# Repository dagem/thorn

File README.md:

# thorn
A no-nonsense macropad with a rosy theme

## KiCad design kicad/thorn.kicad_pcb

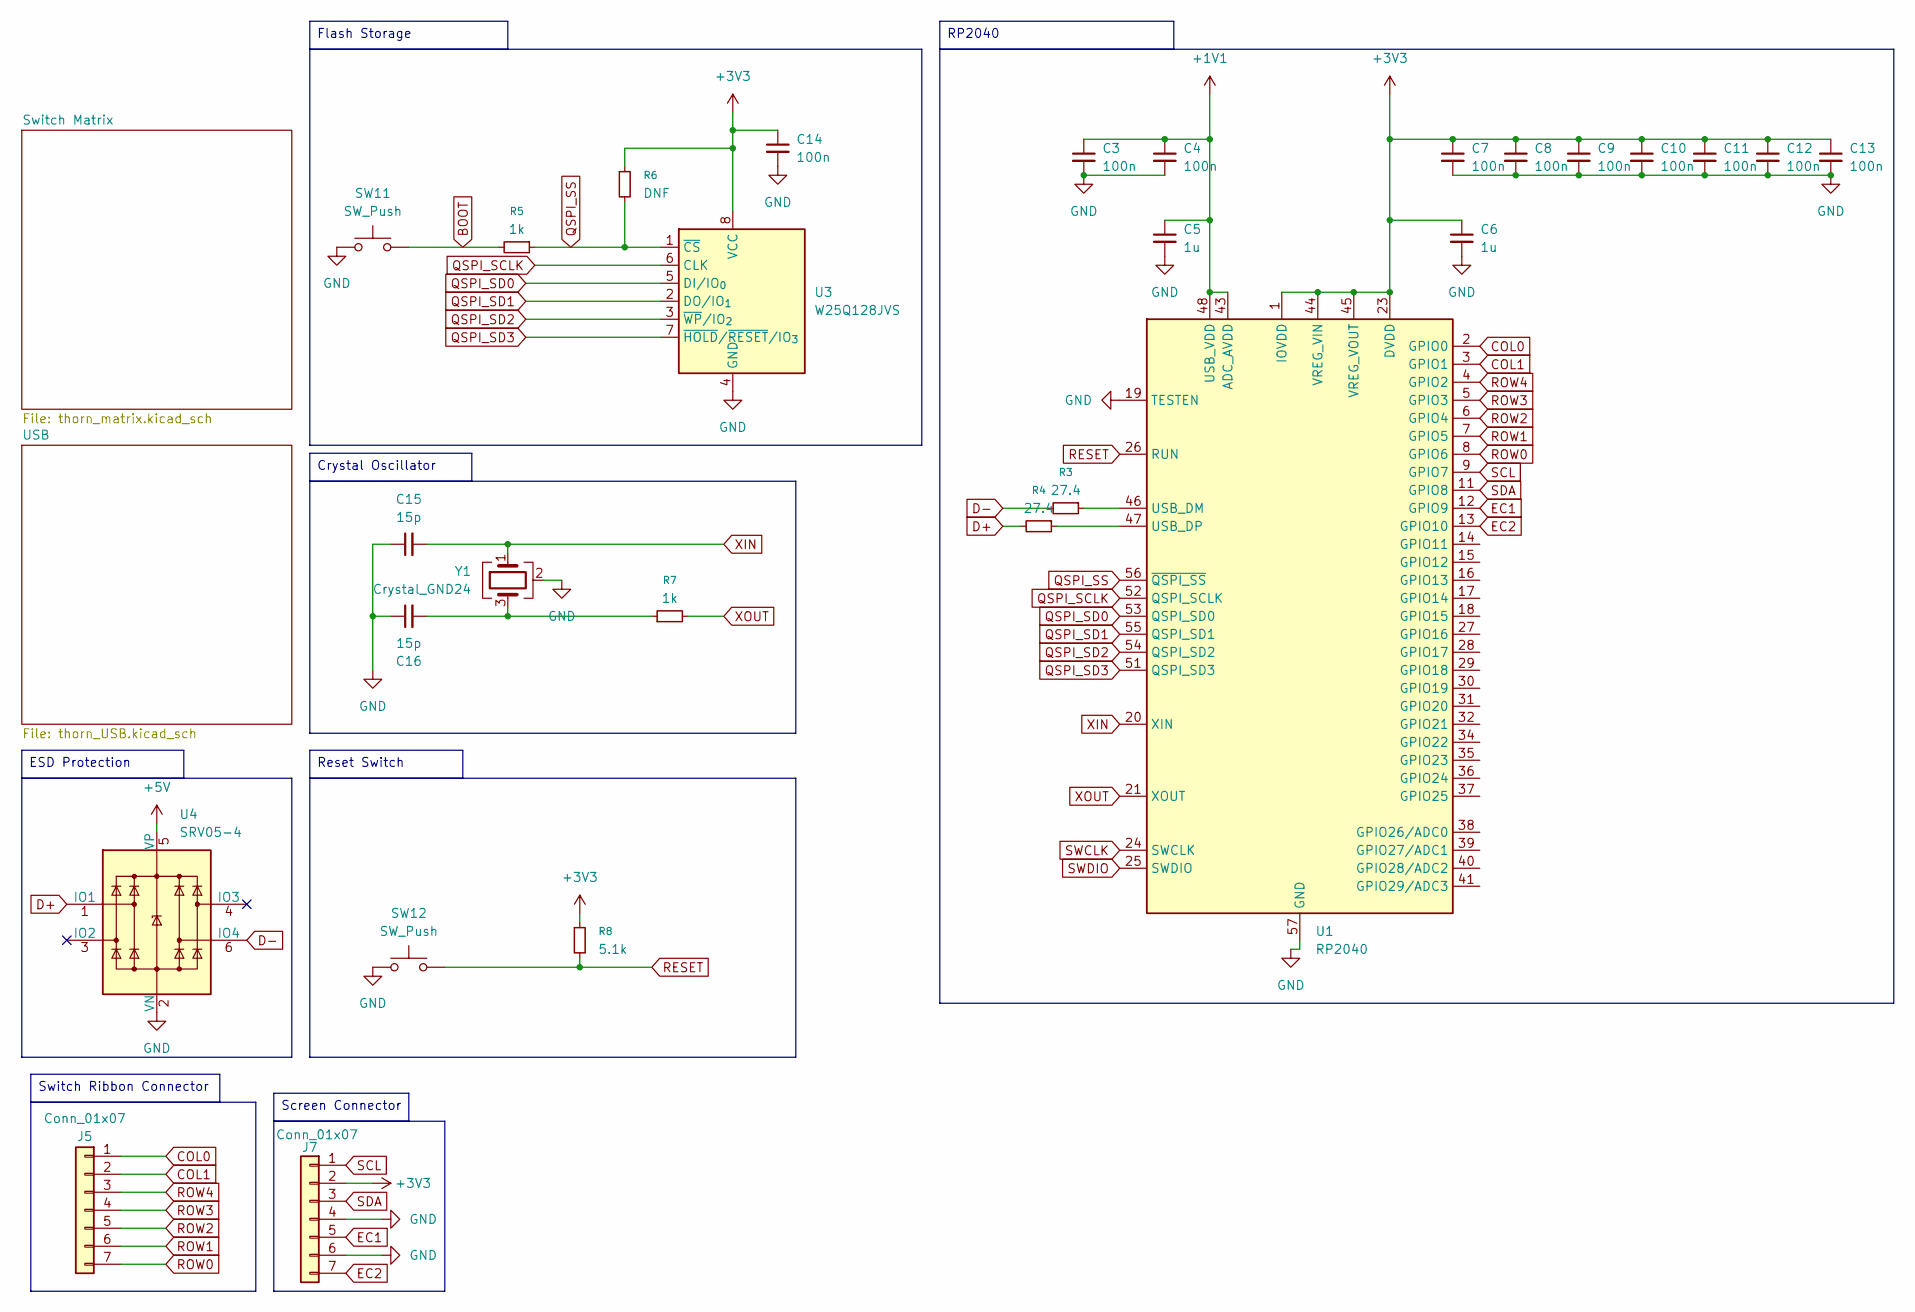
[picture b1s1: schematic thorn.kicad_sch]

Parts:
C3, C4, C7, C8, C9, C10, C11, C12, C13, C14: 100n; C_0805_2012Metric
C5, C6: 1u; C_0805_2012Metric
C15, C16: 15p; C_0805_2012Metric
J5, J7: Conn_01x07; Molex_200528-0070_1x07-1MP_P1.00mm_Horizontal
R3, R4: 27.4; R_0805_2012Metric
R5, R7: 1k; R_0805_2012Metric
R6: DNF; R_0805_2012Metric
R8: 5.1k; R_0805_2012Metric
SW11, SW12: SW_Push; SW_Push_1P1T_XKB_TS-1187A
U1: RP2040; QFN-56-1EP_7x7mm_P0.4mm_EP3.2x3.2mm
U3: W25Q128JVS; SOIC-8_5.3x5.3mm_P1.27mm
U4: SRV05-4; SOT-23-6
Y1: Crystal_GND24; Crystal_SMD_3225-4Pin_3.2x2.5mm

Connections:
+1V1: C3.1, C4.1, C5.1, U1.43 (ADC_AVDD), U1.48 (USB_VDD)
+3V3: C6.1, C7.1, C8.1, C9.1, C10.1, C11.1, C12.1, C13.1, C14.1, J7.2, R6.1, R8.1, U1.1 (IOVDD), U1.10 (IOVDD), U1.22 (IOVDD), U1.23 (DVDD), U1.33 (IOVDD), U1.42 (IOVDD), U1.44 (VREG_VIN), U1.45 (VREG_VOUT), U1.49 (IOVDD), U1.50 (DVDD), U3.8 (VCC); also elsewhere on the board
+5V: U4.5 (VP)
BOOT: R5.2, SW11.2
COL0: J5.1, U1.2 (GPIO0); also elsewhere on the board
COL1: J5.2, U1.3 (GPIO1); also elsewhere on the board
D+: R4.2, U4.1 (IO1); also elsewhere on the board
D-: R3.2, U4.6 (IO4); also elsewhere on the board
EC1: J7.5, U1.12 (GPIO9); also elsewhere on the board
EC2: J7.7, U1.13 (GPIO10); also elsewhere on the board
GND: C3.2, C4.2, C5.2, C6.2, C7.2, C8.2, C9.2, C10.2, C11.2, C12.2, C13.2, C14.2, C15.1, C16.1, J7.4, J7.6, SW11.1, SW12.1, U1.19 (TESTEN), U1.57 (GND), U3.4 (GND), U4.2 (VN), Y1.2 (G), Y1.4 (G); also elsewhere on the board
unnamed: C16.2, R7.1, Y1.3
unnamed: R3.1, U1.46 (USB_DM)
unnamed: R4.1, U1.47 (USB_DP)
QSPI_SCLK: U1.52 (QSPI_SCLK), U3.6 (CLK)
QSPI_SD0: U1.53 (QSPI_SD0), U3.5 (DI/IO_{0})
QSPI_SD1: U1.55 (QSPI_SD1), U3.2 (DO/IO_{1})
QSPI_SD2: U1.54 (QSPI_SD2), U3.3 (~WP/IO_{2})
QSPI_SD3: U1.51 (QSPI_SD3), U3.7 (~HOLD/~RESET/IO_{3})
QSPI_SS: R5.1, R6.2, U1.56 (~QSPI_SS), U3.1 (~CS)
RESET: R8.2, SW12.2, U1.26 (RUN)
ROW0: J5.7, U1.8 (GPIO6); also elsewhere on the board
ROW1: J5.6, U1.7 (GPIO5); also elsewhere on the board
ROW2: J5.5, U1.6 (GPIO4); also elsewhere on the board
ROW3: J5.4, U1.5 (GPIO3); also elsewhere on the board
ROW4: J5.3, U1.4 (GPIO2); also elsewhere on the board
SCL: J7.1, U1.9 (GPIO7); also elsewhere on the board
SDA: J7.3, U1.11 (GPIO8); also elsewhere on the board
SWCLK: U1.24 (SWCLK)
SWDIO: U1.25 (SWDIO)
XIN: C15.2, U1.20 (XIN), Y1.1
XOUT: R7.2, U1.21 (XOUT)

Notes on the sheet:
Switch Ribbon Connector
Crystal Oscillator
Flash Storage
ESD Protection
RP2040
Screen Connector
Reset Switch

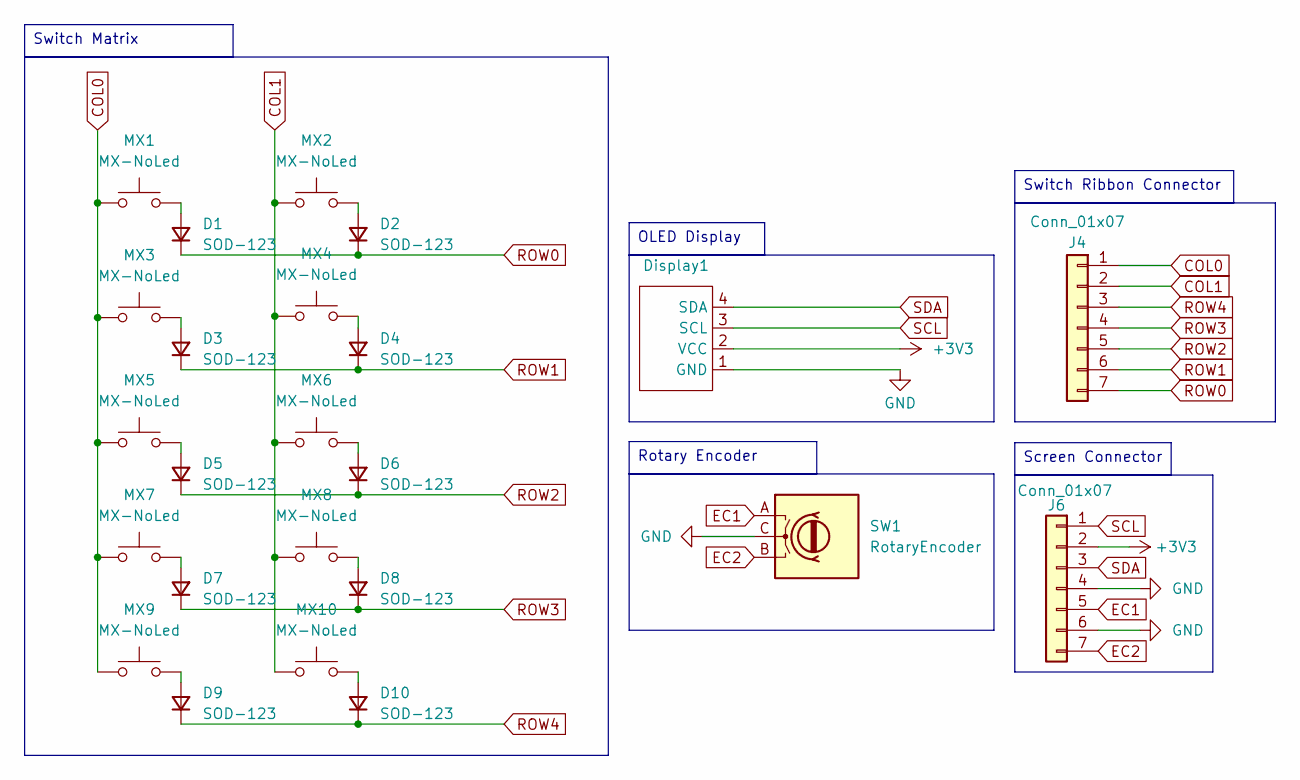
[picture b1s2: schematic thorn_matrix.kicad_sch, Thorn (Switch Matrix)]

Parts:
D1, D2, D3, D4, D5, D6, D7, D8, D9, D10: SOD-123; D_SOD-123
Display1: HS91L02W2C01
J4, J6: Conn_01x07; Molex_200528-0070_1x07-1MP_P1.00mm_Horizontal
MX1, MX2, MX3, MX4, MX5, MX6, MX7, MX8, MX9, MX10: MX-NoLed; MXOnly-1U-NoLED
SW1: RotaryEncoder; RotaryEncoder_Alps_EC12E_Vertical_H20mm

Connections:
+3V3: Display1.2 (VCC), J6.2; also elsewhere on the board
COL0: J4.1, MX1.1, MX3.1, MX5.1, MX7.1, MX9.1; also elsewhere on the board
COL1: J4.2, MX2.1, MX4.1, MX6.1, MX8.1, MX10.1; also elsewhere on the board
EC1: J6.5, SW1.A; also elsewhere on the board
EC2: J6.7, SW1.B; also elsewhere on the board
GND: Display1.1 (GND), J6.4, J6.6, SW1.C; also elsewhere on the board
unnamed: D1.2 (A), MX1.2
unnamed: D2.2 (A), MX2.2
unnamed: D3.2 (A), MX3.2
unnamed: D4.2 (A), MX4.2
unnamed: D5.2 (A), MX5.2
unnamed: D6.2 (A), MX6.2
unnamed: D7.2 (A), MX7.2
unnamed: D8.2 (A), MX8.2
unnamed: D9.2 (A), MX9.2
unnamed: D10.2 (A), MX10.2
ROW0: D1.1 (K), D2.1 (K), J4.7; also elsewhere on the board
ROW1: D3.1 (K), D4.1 (K), J4.6; also elsewhere on the board
ROW2: D5.1 (K), D6.1 (K), J4.5; also elsewhere on the board
ROW3: D7.1 (K), D8.1 (K), J4.4; also elsewhere on the board
ROW4: D9.1 (K), D10.1 (K), J4.3; also elsewhere on the board
SCL: Display1.3 (SCL), J6.1; also elsewhere on the board
SDA: Display1.4 (SDA), J6.3; also elsewhere on the board

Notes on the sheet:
OLED Display
Switch Ribbon Connector
Screen Connector
Rotary Encoder
Switch Matrix

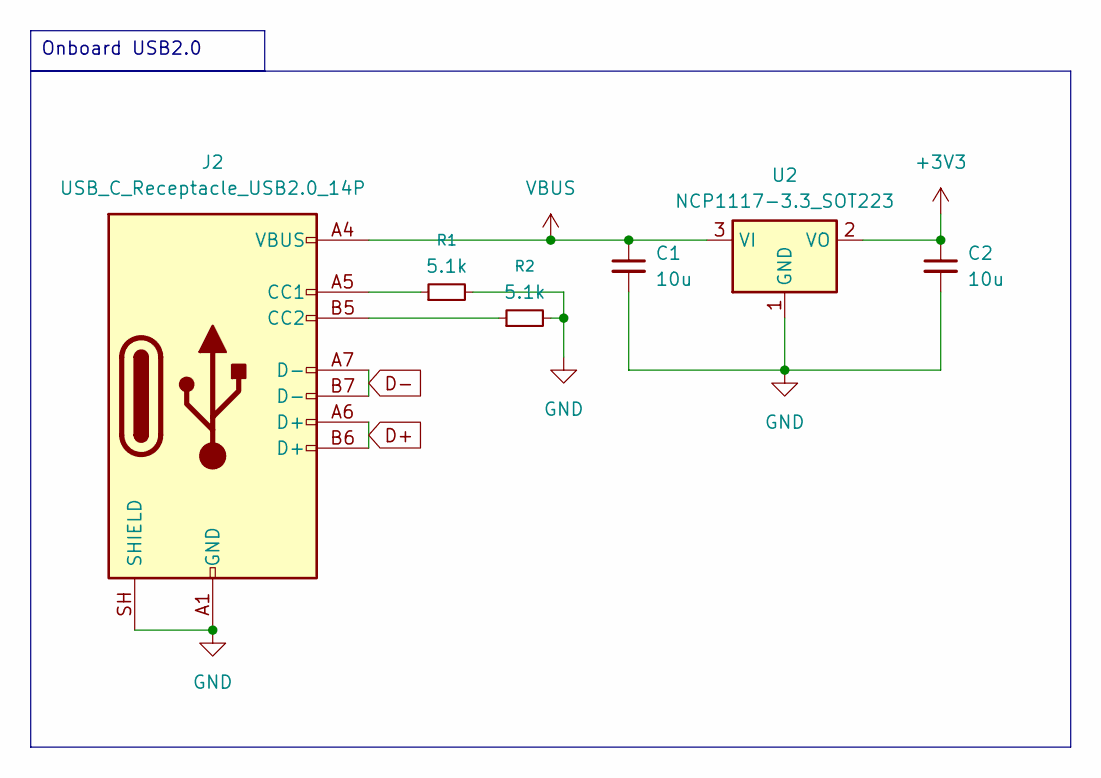
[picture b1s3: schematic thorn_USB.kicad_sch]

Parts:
C1, C2: 10u; C_0805_2012Metric
J2: USB_C_Receptacle_USB2.0_14P; USB_C_Receptacle_JAE_DX07S016JA1R1500
R1, R2: 5.1k; R_0805_2012Metric
U2: NCP1117-3.3_SOT223; SOT-223-3_TabPin2

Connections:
+3V3: C2.1, U2.2 (VO); also elsewhere on the board
D+: J2.A6 (D+), J2.B6 (D+); also elsewhere on the board
D-: J2.A7 (D-), J2.B7 (D-); also elsewhere on the board
GND: C1.2, C2.2, J2.A1 (GND), J2.A12 (GND), J2.B1 (GND), J2.B12 (GND), J2.SH (SHIELD), R1.2, R2.2, U2.1 (GND); also elsewhere on the board
unnamed: J2.A5 (CC1), R1.1
unnamed: J2.B5 (CC2), R2.1
VBUS: C1.1, J2.A4 (VBUS), J2.A9 (VBUS), J2.B4 (VBUS), J2.B9 (VBUS), U2.3 (VI)

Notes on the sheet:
Onboard USB2.0

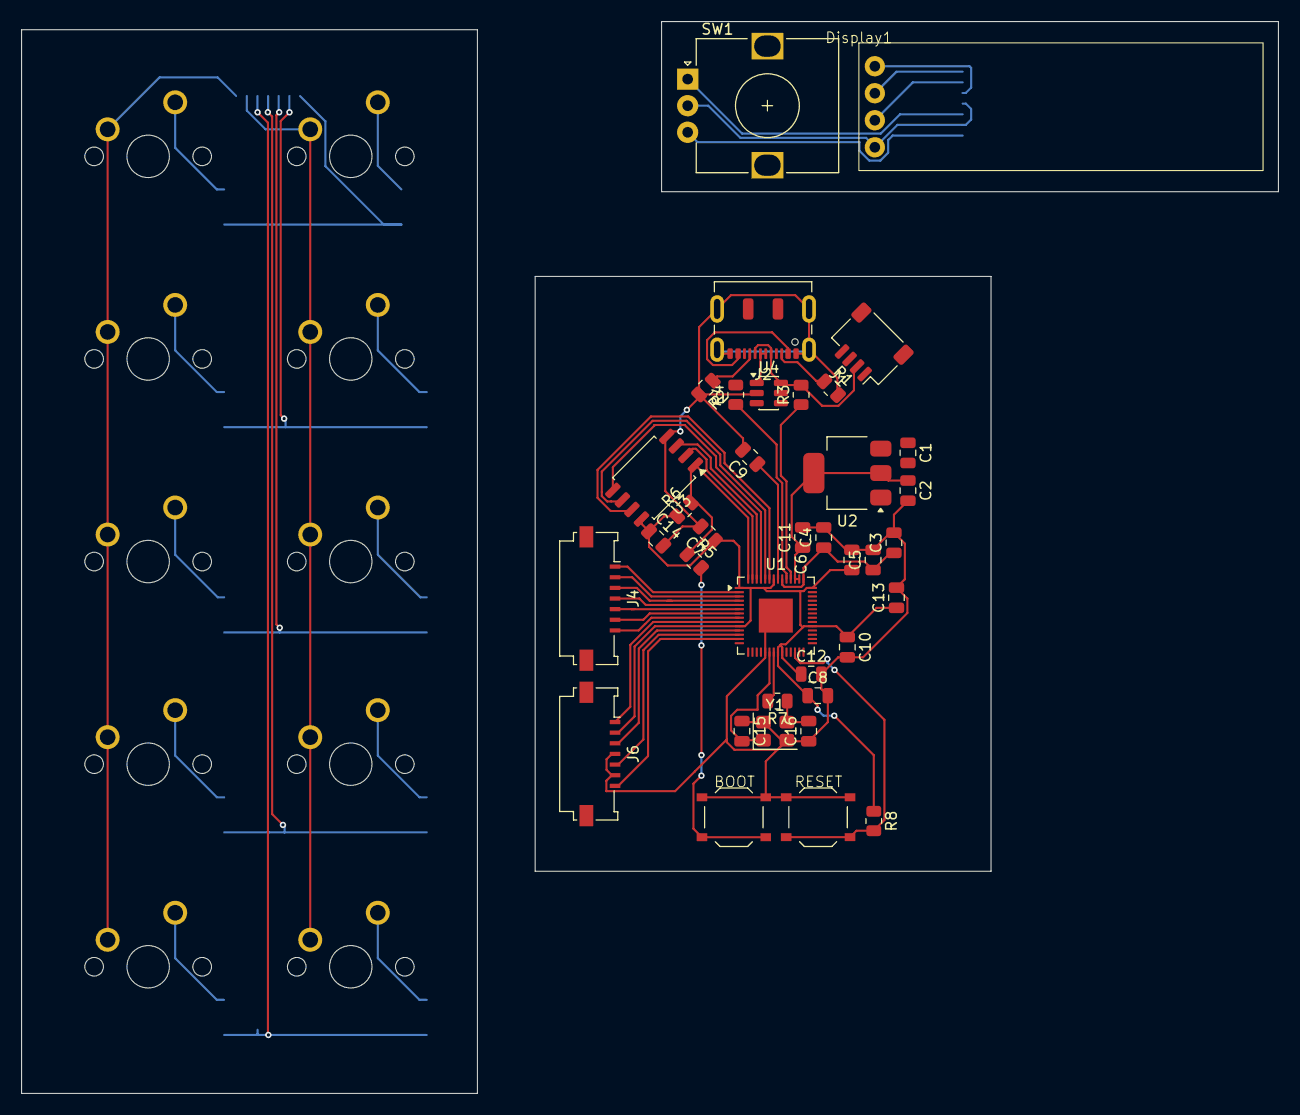
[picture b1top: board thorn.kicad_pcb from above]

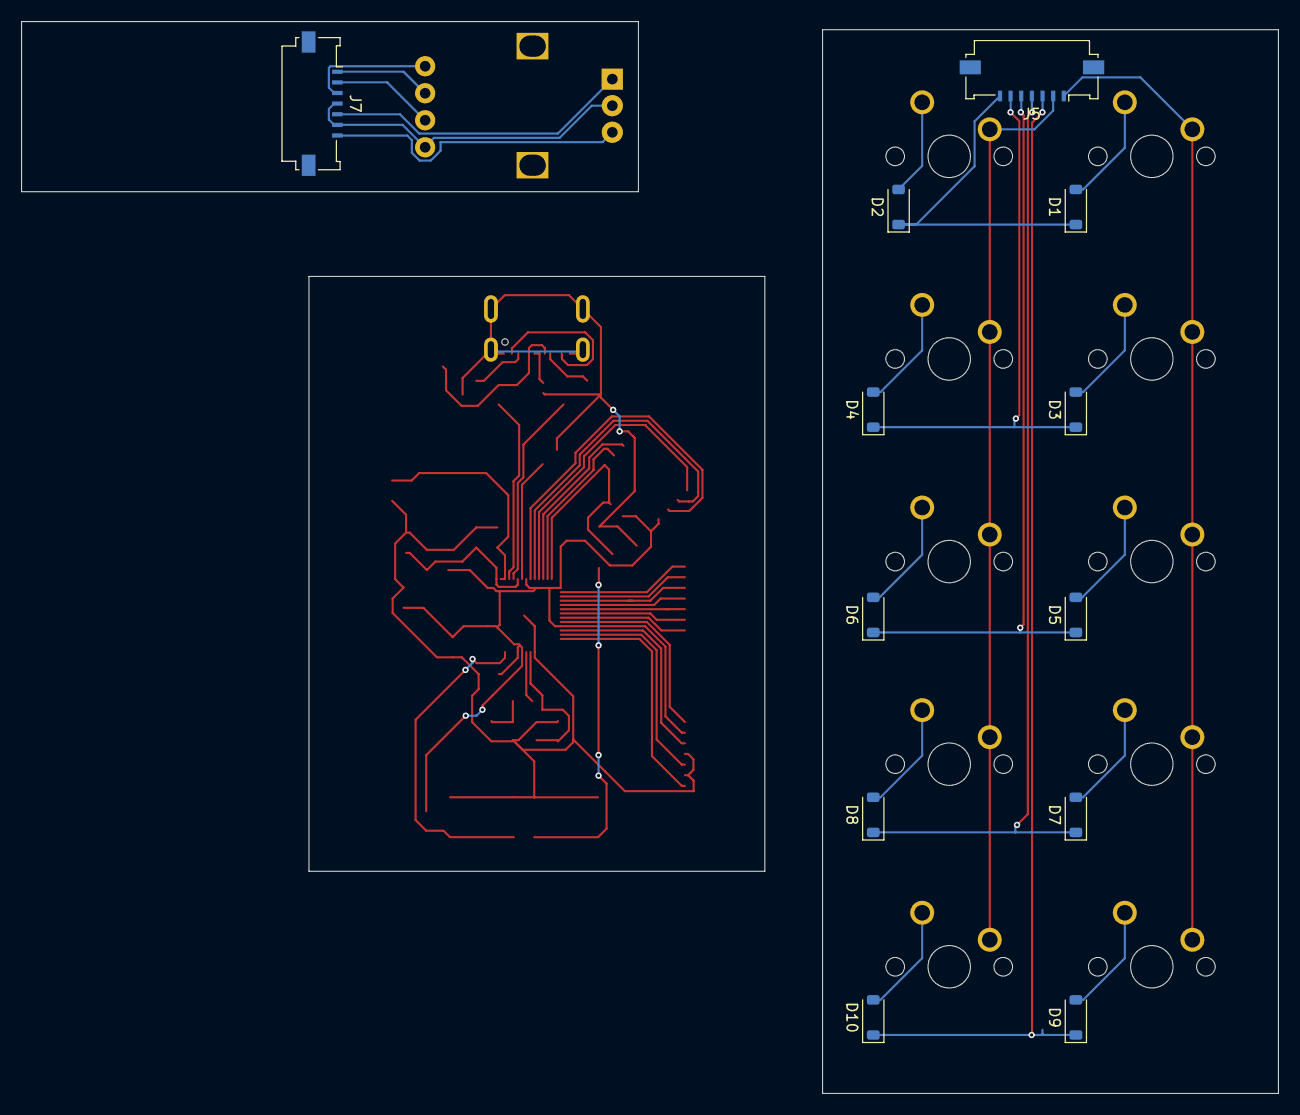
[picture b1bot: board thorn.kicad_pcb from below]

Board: 2 copper layers, 118.2 x 100.8 mm, 59 parts (12 on the bottom side), 42 nets.

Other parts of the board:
J1: Conn_01x04; JST_SH_SM04B-SRSS-TB_1x04-1MP_P1.00mm_Horizontal

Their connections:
D+: J1.3; also elsewhere on the board
D-: J1.2; also elsewhere on the board
GND: J1.4; also elsewhere on the board

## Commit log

2026-01-26 feat: complete design for macropad with kb2040 implementation
2026-01-26 chore: removed '.DS_Store' files from repository
2026-01-26 chore: cleaned up directories
2026-01-28 fix: changed pinout for data pins on JST connector
2026-01-28 fix: removed DS_Store files
2026-04-06 feat: change design to implement rp2040
2026-04-07 chore: cleaned up schematic
2026-04-07 feat: finished preliminary wiring
2026-04-08 feat: change pcb to preliminary final design
